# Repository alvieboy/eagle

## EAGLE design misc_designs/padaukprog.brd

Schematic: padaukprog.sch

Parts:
BOOT1, BOOT2: PIN-1X2
C1, C2, C3, C4, C7, C22, C24, C27, C47, C56: 100nF 6.3V; 0603
C5, C6, C41, C44: 22uF 16V; 0805
C8, C10, C11, C15, C29, C30, C33, C34, C35, C45, C50, C54, C64, C68, C69, C70, C71, C73, C74, C75, C76, C77, C80: 100nF; 0603
C9, C25, C26, C53, C57, C60, C63, C66: 100nF 50V; 0603
C12, C17, C18, C38, C48: 10uF; 0603
C13: 2.2uF 50V; 0805
C14: 2.2uF; 0603
C16: 2.2uF; 0805
C19, C20: 16pF 6.3V; 0603
C21, C36, C46, C61: 1uF; 0603
C23: 1nF; 0603
C28: 100nF/DNP; 0603
C31, C32, C81, C82: 20pF 6.3V; 0603
C37, C42, C51, C55, C62, C72, C78: 10uF; 0805
C39, C40, C67: 22uF; 0805
C43, C49, C52: 10uF 6.3V; 0603
C58, C59: 22uF 50V; 0805
C65, C79: 10nF; 0603
D1: 1N4148W; SOD-123
D2: 2SS100L-W; SOD-123
D3, D4: RB521S-30; SOD523
H1, H2, H3, H4, H5, H6, H7: MOUNT-PAD-ROUND3.2; 3,2-PAD
IC1: LAN8720A; QFN24_4MM_X_4MM
IC2: LM358D; SO08
IC3: IC_DIL16-SOIC-16; SOIC-16
IC4: TPS62063; WSON8-2.1X2.1
IC5: DIL16; DIL16@1
IC6, IC7: 4051D; SO16
IC8: PFS154-S16; SOIC16-N
IC9: MIC550X; SOT23-5L
J1, J4: JST-PH 2mm; JST-2-PTH@1
J2, J5: JUMPER_SOLDER_1X2
J3: JACK-PLUG; SPC4078-NOSLOT
J6: AVR_SPI_PRG_6NS; 2X3-NS
JP1, JP2, JP3, JP5, JP6, JP7, JP8, JP9: PIN-1X2
JP4: PIN-1X3
JP10: VBat +; PIN-1X2
JP11: Pedal; PIN-1X2
JP12, JP13: PIN-1X8
L1, L2, L3, L8, L9: 10uH; 0805
L4, L5, L7, L11, L12, L14: 600R; 0805
L6: 150nH; 0805
L10, L13: DFE252012F; L2520
LED1, LED2, LED3, LED4, LED5, LED6: LG L29K-G2J1-24; LED-603
M1, M2, M3: XT1861B; SOT23
P1, P2: B3B-PH-K
Q1, Q2, Q3, Q5, Q7, Q10: BSS84; SOT23
Q4: 25MHz; HC49U-V
Q6, Q11: 8MHz; HC49U-V
Q8: BSS123; SOT23
Q9: FDN338; SUPER-SOT3
R1: 470K; 0603
R2, R5, R8, R9, R10, R38, R42, R45: 2K2; 0603
R3, R4, R6, R7, R11, R22, R25, R36, R43, R52, R74, R75, R76, R81, R82, R83: 10K; 0603
R12, R14, R47, R48, R78, R79: 20R; 0603
R13, R15, R16, R17, R18, R19, R20, R21, R54, R55: 330R; 0603
R23, R24, R73: 240K; 0603
R26, R27, R28, R32, R34: 20K; 0603
R29, R64: 6K2; 0603
R30: 12K1; 0603
R31, R33, R63: 100K; 0603
R35, R37: 2K2/DNP; 0603
R39, R41, R44, R46: 49R9; 0603
R40, R65, R66, R67, R69: 0R; 0603
R49, R68, R70: 0R/DNP; 0603
R50, R51, R56, R57, R58, R59, R60, R61, R62: 100R; 0603
R53, R71, R72, R77, R80: 1K5/DNP; 0603
S1, S2, S3: SWITCHES_-SMD-1101NE; TACTILE-SWITCH-1101NE
SJ1: SOLDERJUMPERNC; SJ_2S_SMALL
T1: Hanrun HR917550A; HR13550A
TP11, TP12, TP13: TPPAD1-13; P1-13
TP14, TP15, TP16, TP17, TP18: TPTP07SQ; TP07SQ
TP20, TP21, TP22, TP23, TP24, TP25, TP26, TP27, TP28, TP29: TPTP12SQ; TP12SQ
U1: STM32F107RCT6; QFP50P1200X1200X160-64N
U2: ESP-WROOM-32
U3: MIC550X; SOT23-5L
U4: ATTINY24A-SSU; SOIC127P600X175-14N
U$1, U$8, U$10, U$12, U$22, U$30: PIN-1X4
U$2: STM32F072CBT6; LQFP48
U$3: SR410361N; LCD_7SEG_4DIGIT
U$4: STM8S003F3P6; TSSOP20
U$5: P25QXH; SOIC8
U$6, U$11, U$21, U$23: PIN-1X8
U$7, U$20: PFS154-S16; SOIC16-N
U$9: TSSOP16
U$13: PMS150C-U06; SOT23-6
U$14: AP2000; SOT23-6
U$15: MT3608; SOT23-6
U$16, U$17, U$18, U$26, U$27: PIN-1X10
U$19: STM32F030F4P6; TSSOP20
U$25: PN532_NFCB; HW-147-NFC-NOHOLES
U$28: MIC550X; SOT23-5L
U$29: STM32F070F6; TSSOP20
USB1, USB2, USB3: CON-USB-F-MICRO-B; CONN_USB_MICRO-B
VDD: TPTP10R; TP10R
VPP: TPTP10R; TP10R
X1, X2: FH12-40S-0.5SH

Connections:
+3V3: BOOT1.2, BOOT2.2, C1.1, C2.1, C3.1, C4.1, C8.2, C10.2, C11.2, C15.2, C16.2, C17.2, C22.1, C24.1, C27.1, C30.2, C33.2, C38.2, C39.2, C47.1, C48.2, C49.1, C50.2, C52.1, C62.2, C64.2, C65.2, C68.2, C69.2, C76.2, C77.2, C79.2, C80.2, IC1.1 (VDD2A), IC1.9 (VDDIO), IC1.19 (VDD1A), IC4.4 (FB), J2.2, J5.2, JP1.2, JP9.1, L1.1, L5.1, L11.2, L12.1, L13.P$2 (2), LED1.A, LED2.A, LED3.A, LED4.A, LED5.A, LED6.A, M1.3 (VOUT), M3.3 (VOUT), Q1.2 (S), Q2.2 (S), Q3.2 (S), Q5.2 (S), Q7.2 (S), Q9.2 (S), R1.1, R4.2, R6.2, R7.2, R8.2, R10.2, R11.2, R22.2, R25.2, R35.2, R36.2, R37.2, R52.2, R53.2, R54.2, R55.2, R63.1, R75.2, R80.2, R83.2, U1.1 (VBAT), U1.19 (VDD_4), U1.32 (VDD_1), U1.48 (VDD_2), U1.64 (VDD_3), U3.5 (VOUT), U$1.1, U$2.1 (VBAT), U$2.24 (VDD), U$2.36 (VDDIO2), U$2.48 (VDD), U$4.9 (VDD), U$5.3 (NWP), U$5.8 (VCC), U$7.5 (VCC), U$8.1, U$10.4, U$19.16 (VDD), U$22.2, U$23.7, U$25.VCC, U$25.VCC1 (VCC), U$28.5 (VOUT), U$29.5 (VDDA), U$29.16 (VDD), U$30.1, X1.2, X1.3
+5V: C40.2, L7.1, USB2.P1 (VUSB)
+5V_FILT: C43.1, L7.2, Q10.2 (S), R64.2, U3.1 (VIN), U3.3 (EN)
+15V: C9.1, C13.1, C57.1, C58.2, C59.2, D2.C, IC2.8 (V+), R73.2
A_MISO: J6.1, U4.8 (PA5)
A_MOSI: J6.4, U4.7 (PA6)
A_RESET: J6.5, U4.4 (PB3)
A_SCK: J6.3, U4.9 (PA4)
BOOT0: BOOT1.1, R43.2, U$2.38 (PA15), U$2.44 (BOOT0)
CA0: Q1.1 (G), R7.1, U$7.7 (PA6)
CA1: Q2.1 (G), R11.1, U$7.6 (PA7)
CA2: Q3.1 (G), R22.1, U$7.4 (PB7)
CA3: Q5.1 (G), R25.1, U$7.3 (PB6)
CC_RST: U1.39 (PC8), X1.22
CC_RX: U1.53 (PC12), X1.17
CC_SS: U1.40 (PC9), X1.21
CC_TX: U1.54 (PD2), X1.18
ESP_EN: U1.49 (PA14), U2.3 (EN)
ESP_IO0: U1.29 (PB10), U2.25 (IO0)
ESP_MISO: R67.2, R68.2, U2.31 (IO19)
ESP_MOSI: R69.2, R70.2, U2.37 (IO23)
ESP_ON: Q9.1 (G), R63.2
ESP_RX: U1.51 (PC10), U2.34 (RXD0)
ESP_SCK: R66.2, U2.30 (IO18)
ESP_TX: U1.52 (PC11), U2.35 (TXD0)
ESP_VCC: Q9.3 (D), U2.2 (3V3)
F_MISO: U$4.17 (PC7/SPI_MISO/[TIM1_CH2]), U$5.2 (SO)
F_MOSI: U$4.16 (PC6/SPI_MOSI/[TIM1_CH1]), U$5.5 (SI)
F_NCS: U$4.10 (PA3/TIM2_CH3/[SPI_NSS]), U$5.1 (NCS)
F_NHOLD: U$4.1 (PD4/UART1_CK/TIM2_CH1/BEEP), U$5.7 (NHOLD)
F_SCK: U$4.15 (PC5/SPI_SCK/[TIM2_CH1]), U$5.6 (SCK)
GND: C1.2, C2.2, C3.2, C4.2, C5.1, C6.1, C7.2, C8.1, C10.1, C11.1, C12.1, C14.1, C15.1, C16.1, C17.1, C18.1, C19.1, C20.1, C21.1, C22.2, C23.1, C24.2, C25.2, C26.2, C27.2, C28.1, C29.1, C30.1, C31.1, C32.1, C33.1, C34.2, C35.2, C36.1, C37.1, C38.1, C39.1, C40.1, C41.1, C42.1, C43.2, C44.1, C45.1, C46.1, C47.2, C48.1, C49.2, C50.1, C51.1, C52.2, C53.2, C54.1, C55.1, C56.2, C57.2, C58.1, C59.1, C60.2, C61.1, C62.1, C64.1, C65.1, C66.2, C67.1, C68.1, C69.1, C70.2, C71.1, C72.1, C73.2, C74.1, C75.2, C76.1, C77.1, C78.1, C79.1, C80.1, C81.1, C82.1, D4.K, IC1.P (VSS), IC4.1 (PGND), IC4.3 (AGND), IC4.6 (MODE), IC4.EXP (PGND), IC5.12, IC6.7 (VEE), IC6.8 (GND), IC7.7 (VEE), IC7.8 (GND), IC8.12 (GND), IC9.2 (GND), J1.2, J3.1, J4.2, J6.6, JP2.1, JP3.1, JP4.1, JP5.2, JP7.1, JP8.2, JP10.1, JP11.1, M1.1 (GND), M2.1 (GND), M3.1 (GND), P1.1, P2.3, Q8.2 (S), R3.2, R23.1, R24.1, R27.1, R29.1, R30.1, R32.1, R34.1, R43.1, R72.1, R74.1, R76.1, R82.1, S1.P$1 (1), S2.P$2 (2), S3.P$2 (2), TP11.TP, TP12.TP, TP13.TP, U1.12 (VSSA), U1.18 (VSS_4), U1.31 (VSS_1), U1.47 (VSS_2), U1.63 (VSS_3), U2.1 (GND), U2.15 (GND), U2.38 (GND), U2.GND, U3.2 (GND), U4.14 (GND), U$1.4, U$2.8 (VSSA), U$2.23 (VSS), U$2.35 (VSS), U$2.47 (VSS), U$4.7 (VSS), U$5.4 (GND), U$7.12 (GND), U$8.4, U$10.1, U$12.3, U$12.4, U$13.2 (GND), U$14.2 (GND), U$15.2 (GND), U$18.1, U$19.15 (VSS), U$20.12 (GND), U$22.1, U$23.8, U$25.GND, U$25.GND1 (GND), U$26.1, U$27.1, U$28.2 (GND), U$29.15 (VSS), U$30.4, USB1.P5 (GND), USB2.P5 (GND), USB3.P5 (GND), X1.4, X1.5, X1.11, X1.29, X1.31, X1.33, X1.35, X1.37, X1.40, X2.4, X2.5, X2.11, X2.29, X2.31, X2.33, X2.35, X2.37, X2.40
LCLK: U$7.11 (PA0), U$10.2
LDAT: U$7.13 (PB0), U$10.3
LED0: R2.2, U$2.2 (PC13)
LED1: R5.2, U$2.3 (PC14/OSC32_IN)
LED2: R9.2, U$2.4 (PC15/OSC32_OUT)
MCO: R40.1, U1.41 (PA8)
MCU_MISO: IC5.7, R59.1, R60.1, U$13.3 (PA6), U$20.7 (PA6)
MCU_MOSI: IC5.10, R61.1, R62.1, U$13.1 (PA4), U$20.10 (PA4)
MCU_PA0: IC5.11, R56.1, TP28.TP, U$20.11 (PA0)
MCU_PA7: IC5.6, R57.1, TP29.TP, U$20.6 (PA7)
MCU_SCK: IC5.9, R58.1, U$13.6 (PA3), U$20.9 (PA3)
MISO: R59.2, R62.2, U$2.40 (PB4)
MOSI: R60.2, R61.2, U$2.41 (PB5)
unnamed: LED2.C, R5.1
unnamed: C44.2, L10.P$1 (1), Q10.3 (D), U$15.4 (EN), U$15.5 (IN)
unnamed: LED3.C, R9.1
unnamed: L2.2, M1.2 (SW)
unnamed: C5.2, J2.1, JP3.2, L2.1
unnamed: TP17.TP, U$4.5 (PA1/OSCIN)
unnamed: C14.2, U$4.8 (VCAP)
unnamed: C29.2, R36.1, U$4.4 (NRST), U$8.2
unnamed: TP18.TP, U$4.6 (PA2/OSCOUT)
unnamed: C45.2, C46.2, L11.1, U$19.5 (VDDA)
unnamed: C36.2, JP6.1, L6.2
unnamed: TP14.TP, U$4.20 (PD3/AIN4/TIM2_CH2/ADC_ETR)
unnamed: C41.2, J4.1, J5.1, L8.1
unnamed: C37.2, JP6.2
unnamed: L6.1, Q7.3 (D), Q8.3 (D)
unnamed: L8.2, M3.2 (SW)
unnamed: L14.1, USB3.P1 (VUSB)
unnamed: Q7.1 (G), R49.1, R50.1
unnamed: Q8.1 (G), R51.1
unnamed: R12.1, USB1.P2 (D-)
unnamed: LED1.C, R2.1
unnamed: R14.1, USB1.P3 (D+)
unnamed: JP9.2, R76.2, U$19.1 (BOOT0)
unnamed: U$12.1, X2.1
unnamed: R65.2, U2.29 (IO5)
unnamed: LED4.C, R38.1
unnamed: LED5.C, R42.1
unnamed: LED6.C, R45.1
unnamed: R78.1, USB3.P2 (D-)
unnamed: IC5.16, TP23.TP
unnamed: IC5.15, TP22.TP
unnamed: IC5.14, TP21.TP
unnamed: R79.1, USB3.P3 (D+)
unnamed: IC6.3 (X), IC7.3 (X)
unnamed: IC5.13, TP20.TP
unnamed: R47.1, USB2.P2 (D-)
unnamed: R48.1, USB2.P3 (D+)
unnamed: IC6.4 (X7), JP12.1
unnamed: L4.1, USB1.P1 (VUSB)
unnamed: IC1.24 (RBIAS), R30.2
unnamed: C6.2, J1.1, L3.1
unnamed: R73.1, R74.2, U$15.3 (FB)
unnamed: C63.2, D3.K, D4.A
unnamed: C35.1, T1.5
unnamed: C34.1, T1.4
unnamed: R54.1, T1.12 (A)
unnamed: L3.2, M2.2 (SW)
unnamed: C18.2, JP5.1, M2.3 (VOUT)
unnamed: IC7.13 (X0), JP13.8
unnamed: IC2.6 (-IN), R28.2, R29.2
unnamed: IC2.2 (-IN), R26.2, R27.2
unnamed: IC6.13 (X0), JP12.8
unnamed: R55.1, T1.9 (A)
unnamed: IC5.1, TP24.TP
unnamed: IC5.2, TP25.TP
unnamed: C28.2, L5.2, R39.2, R41.2, R44.2, R46.2
unnamed: IC5.3, TP26.TP
unnamed: C21.2, C23.2, IC1.6 (VDDCR)
unnamed: IC5.4, TP27.TP
unnamed: IC6.14 (X1), JP12.7
unnamed: IC6.12 (X3), JP12.5
unnamed: IC6.1 (X4), JP12.4
unnamed: IC6.5 (X5), JP12.3
unnamed: IC6.2 (X6), JP12.2
unnamed: Q2.3 (D), U$3.9 (CA1)
unnamed: J6.2, SJ1.2
unnamed: IC7.14 (X1), JP13.7
unnamed: IC7.15 (X2), JP13.6
unnamed: IC7.12 (X3), JP13.5
unnamed: IC6.15 (X2), JP12.6
unnamed: IC7.1 (X4), JP13.4
unnamed: IC7.5 (X5), JP13.3
unnamed: IC7.2 (X6), JP13.2
unnamed: IC7.4 (X7), JP13.1
unnamed: Q3.3 (D), U$3.8 (CA2)
unnamed: Q1.3 (D), U$3.12 (CA0)
unnamed: Q5.3 (D), U$3.6 (CA3)
unnamed: U$12.2, U$17.1, X2.2, X2.3
unnamed: IC3.8, U$6.1, U$9.1
unnamed: IC3.7, U$6.2, U$9.2
unnamed: IC3.6, U$6.3, U$9.3
unnamed: IC3.5, U$6.4, U$9.4
unnamed: IC3.4, U$6.5, U$9.5
unnamed: IC3.3, U$6.6, U$9.6
unnamed: IC3.2, U$6.7, U$9.7
unnamed: IC3.1, U$6.8, U$9.8
unnamed: IC3.16, U$9.9, U$11.8
unnamed: IC3.15, U$9.10, U$11.7
unnamed: IC3.13, U$9.12, U$11.5
unnamed: IC3.14, U$9.11, U$11.6
unnamed: IC3.12, U$9.13, U$11.4
unnamed: IC3.11, U$9.14, U$11.3
unnamed: IC3.10, U$9.15, U$11.2
unnamed: IC3.9, U$9.16, U$11.1
NBOOT0: BOOT2.1, R82.2, U$29.1 (BOOT0)
NIRQ: U$25.IRQ, U$29.7 (PA1)
NLED0: R38.2, U1.46 (PA13)
NLED1: R42.2, U1.35 (PB14)
NLED2: R45.2, U1.36 (PB15)
NNRST: R83.1, S3.P$1 (1), U$29.4 (NRST)
NOSC_IN: C81.2, Q11.2, U$29.2 (PF0/OSC_IN)
NOSC_OUT: C82.2, Q11.1, U$29.3 (PF1/OSC_OUT)
NRST: R52.1, S2.P$1 (1), U$2.7 (NRST)
NRSTO: U$25.RSTO, U$29.6 (PA0)
NSWCLK: U$29.20 (PA14), U$30.3
NSWDIO: U$29.19 (PA13), U$30.2
NUSBDM: R78.2, U$29.17 (PA9/PA11)
NUSBDP: R79.2, R80.1, U$29.18 (PA10/PA12)
N_MISO: U$25.MISO, U$29.12 (PA6)
N_MOSI: U$25.MOSI, U$29.13 (PA7)
N_RX: U$25.SDA/TX, U$29.9 (PA3)
N_SCK: U$25.SCK, U$29.11 (PA5)
N_SS: U$25.SS, U$29.10 (PA4)
N_TX: U$25.SCL/RX, U$29.8 (PA2)
OSC_IN: C31.2, Q6.2, U$2.5 (PF0/OSC_IN)
OSC_OUT: C32.2, Q6.1, U$2.6 (PF1/OSC_OUT)
PA0: U$19.6 (PA0), U$23.3
PA1: U$19.7 (PA1), U$23.2
PA2: U$19.8 (PA2), U$23.1
PA3: U$19.9 (PA3), U$21.8
PA3/ADC3: U1.17 (PA3), X1.30
PA4: U$19.10 (PA4), U$21.7
PA4/DAC1: U1.20 (PA4), X1.32
PA5: U$19.11 (PA5), U$21.6
PA5/DAC2: U1.21 (PA5), X1.34
PA6: U$19.12 (PA6), U$21.5
PA7: U$19.13 (PA7), U$21.4
PA9: P2.2, U$19.17 (PA9)
PA10: P2.1, U$19.18 (PA10)
PA13: U$19.19 (PA13/SWDIO), U$21.2
PA14: U$19.20 (PA14/SWCLK), U$21.1
PA15/NSS: R65.1, U1.50 (PA15)
PB1: U$19.14 (PB1), U$21.3
PB6/UART1_TX: U1.58 (PB6), X1.12
PB7/UART1_RX: U1.59 (PB7), X1.13
PEDAL: JP11.2, R81.1, U4.5 (PB2)
PF0: U$19.2 (PF0/OSC_IN), U$23.6
PF1: U$19.3 (PF1/OSC_OUT), U$23.5
PHY_LED0: IC1.3 (LED1/REGOFF), T1.10 (K)
PHY_LED1: IC1.2 (LED2/NINTSEL), T1.11 (K)
PWM1: R50.2, R51.2, U$4.13 (PC3/TIM1_CH3/[TIM1_CH1N])
PWM2: R49.2, U$4.14 (PC4/TIM1_CH4/CLK_CCO/AIN2/[TIM1_CH2N])
PWRON: Q10.1 (G), R64.1, U$2.27 (PB14)
REG33IN: C51.2, D1.1 (C), IC4.5 (EN), IC4.7 (AVIN), IC4.8 (PVIN), J3.3, X1.1
RMII_CRS_DV: IC1.11 (CRS_DV/MODE2), U1.23 (PA7)
RMII_MDC: IC1.13 (MDC), R8.1, U1.9 (PC1)
RMII_MDIO: IC1.12 (MDIO), R10.1, U1.16 (PA2)
RMII_NRST: IC1.15 (NRST), R4.1, U1.22 (PA6)
RMII_REF_CLK: IC1.14 (NINT/REFCLK0), U1.15 (PA1)
RMII_RXD0: IC1.8 (RXD0/MODE0), U1.24 (PC4)
RMII_RXD1: IC1.7 (RXD1/MODE1), U1.25 (PC5)
RMII_TXD0: IC1.17 (TXD0), U1.33 (PB12)
RMII_TXD1: IC1.18 (TXD1), U1.34 (PB13)
RMII_TX_EN: IC1.16 (TXEN), U1.30 (PB11)
RX: JP4.2, U$4.3 (PD6/UART1_RX/AIN6)
RXM1: IC1.20 (TXN), R41.1, T1.2
RXP1: IC1.21 (TXP), R39.1, T1.1
S0: U$16.1, X2.6
S1: U$18.2, X2.7
S2: U$17.2, X2.8
S3: U$16.2, X2.9
S4: U$18.3, X2.10
S5: U$17.3, X2.12
S6: U$16.3, X2.13
S7: U$18.4, X2.14
S8: U$17.4, X2.15
S9: U$16.4, X2.16
S10: U$18.5, X2.17
S11: U$17.5, X2.18
S12: U$16.5, X2.19
S13: U$18.6, X2.20
S14: U$17.6, X2.21
S15: U$16.6, X2.22
S16: U$18.7, X2.23
S17: U$17.7, X2.24
S18: U$16.7, X2.25
S19: U$18.8, X2.26
S20: U$17.8, X2.27
S21: U$16.8, X2.28
S22: U$18.9, X2.30
S23: U$17.9, X2.32
S24: U$16.9, X2.34
S25: U$18.10, X2.36
S26: U$17.10, X2.38
S27: U$16.10, X2.39
SA: R13.2, U$3.11 (A)
SB: R15.2, U$3.7 (B)
SC: R16.2, U$3.4 (C)
SCK: R58.2, U$2.39 (PB3)
SCL: TP15.TP, U$4.12 (PB4/I2C_SCL/ADC_ETR)
SD: R17.2, U$3.2 (D)
SDA: TP16.TP, U$4.11 (PB5/I2C_SDA/[TIM1_BKIN])
SDP: R21.2, U$3.3 (DP)
SE: R18.2, U$3.1 (E)
SEG_A: R13.1, U$7.9 (PA3)
SEG_B: R15.1, U$7.14 (PB1)
SEG_C: R16.1, U$7.2 (PB5)
SEG_D: R17.1, U$7.15 (PB2)
SEG_DP: R21.1, U$7.16 (PB3)
SEG_E: R18.1, U$7.10 (PA4)
SEG_F: R19.1, U$7.8 (PA5)
SEG_G: R20.1, U$7.1 (PB4)
SEL_A0: IC7.11 (A), U4.10 (PA3)
SEL_A1: IC6.11 (A), U4.13 (PA0)
SEL_B0: IC7.10 (B), U4.6 (PA7)
SEL_B1: IC6.10 (B), U4.12 (PA1)
SEL_C0: IC7.9 (C), U4.2 (PB0)
SEL_C1: IC6.9 (C), U4.11 (PA2)
SEL_INH: IC6.6 (INH), IC7.6 (INH), U4.3 (PB1)
SF: R19.2, U$3.10 (F)
SG: R20.2, U$3.5 (G)
SHIELD: T1.8, T1.Z1 (SHIELD), T1.Z2 (SHIELD)
STM_PA0: R56.2, U$2.42 (PB6)
STM_PA7: R57.2, U$2.43 (PB7)
SW: JP2.2, R6.1, U$4.19 (PD2/AIN3/[TIM2_CH3])
SWCLK: U$1.3, U$2.37 (PA14)
SWDIO: U$1.2, U$2.34 (PA13)
SWIM: U$4.18 (PD1/SWIM), U$8.3
S_FB: R71.1, R72.2, U$14.3 (FB)
S_SW: L9.2, U$14.1 (SW)
S_VIN: C42.2, JP7.2, L9.1, U$14.4 (SHDN), U$14.6 (VIN)
S_VOUT: C54.2, C55.2, JP8.1, R71.2, U$14.5 (VOUT)
TX: JP4.3, U$4.2 (PD5/UART1_TX/AIN5)
TXM1: IC1.22 (RXN), R46.1, T1.6
TXP1: IC1.23 (RXP), R44.1, T1.3
UART1RX: U1.43 (PA10), X1.19
UART1TX: U1.42 (PA9), X1.20
UART_RX: P1.2, U$2.31 (PA10)
UART_TX: P1.3, U$2.30 (PA9)
USBDM: R47.2, U$2.32 (PA11)
USBDP: R48.2, R53.1, U$2.33 (PA12)
USBPWR: D1.2 (A), L4.2
USBPWR1: C78.2, L14.2, U$28.1 (VIN), U$28.3 (EN)
VCC3: C71.2, C74.2, IC8.5 (VCC), IC9.5 (VOUT), R77.2, U$26.9, U$26.10
VCCI: C67.2, IC9.1 (VIN), IC9.3 (EN), R77.1, U$27.9, U$27.10
VDDA: C56.1, L12.2, U$2.9 (VDDA)
VDD_OUT: C25.1, C53.1, IC2.1 (OUT), IC5.5, R26.1, R33.2, U$13.5 (VCC), U$20.5 (VCC), VDD.TP
VDD_PWM: IC2.3 (+IN), R23.2, U$2.15 (PA5)
VDD_SENS: R33.1, R34.2, U$2.19 (PB1)
VEE: C9.2, C13.2, C66.1, D3.A, IC2.4 (V-)
VNEG_PWM: C63.1, U$2.13 (PA3)
VPP_OUT: C26.1, C60.1, IC2.7 (OUT), IC5.8, R28.1, R31.2, U$13.4 (PA5), U$20.8 (PA5), VPP.TP
VPP_PWM: IC2.5 (+IN), R24.2, U$2.14 (PA4)
VPP_SENS: R31.1, R32.2, U$2.18 (PB0)
VSW: D2.A, L10.P$2 (2), U$15.1 (SW)
V_BATT: C70.1, C72.2, C73.1, C75.1, IC6.16 (VCC), IC7.16 (VCC), JP10.2, R81.2, SJ1.1, U4.1 (VCC)
X0: IC8.1 (PB4), U$26.2
X1: IC8.2 (PB5), U$26.3
X2: IC8.3 (PB6), U$26.4
X3: IC8.4 (PB7), U$26.5
X4: IC8.6 (PA7), U$26.6
X5: IC8.7 (PA6), U$26.7
X6: IC8.8 (PA5), U$26.8
X7: IC8.16 (PB3), U$27.2
X8: IC8.15 (PB2), U$27.3
X9: IC8.14 (PB1), U$27.4
X10: IC8.13 (PB0), U$27.5
X11: IC8.11 (PA0), U$27.6
X12: IC8.10 (PA4), U$27.7
X13: IC8.9 (PA3), U$27.8
XBOOT0: JP1.1, R3.1, U1.60 (BOOT0)
XI: IC1.5 (XTAL1/CLKIN), R40.2
XNRST: C61.2, R75.1, U$19.4 (NRST), U$23.4
XOSC_IN: C19.2, Q4.2, U1.5 (PD0_OSC_IN)
XOSC_OUT: C20.2, Q4.1, U1.6 (PD1_OSC_OUT)
XPA0: U1.14 (PA0-WKUP), X1.28
XPB0/ADC8: U1.26 (PB0), X1.36
XPB1: U1.27 (PB1), X1.38
XPB2: U1.28 (PB2), X1.39
XPC0: U1.8 (PC0), X1.25
XPC2: U1.10 (PC2), X1.26
XPC3: U1.11 (PC3), X1.27
XPC6: U1.37 (PC6), X1.24
XPC7: U1.38 (PC7), X1.23
XPC13: U1.2 (PC13-TAMPER-RTC), X1.14
XPC14: U1.3 (PC14-OSC32_IN), X1.15
XPC15: U1.4 (PC15-OSC32_OUT), X1.16
XSCL: R35.1, U1.61 (PB8), U$22.3, X1.6
XSDA: R37.1, U1.62 (PB9), U$22.4, X1.7
XSPI_MISO: R67.1, R70.1, U1.56 (PB4), X1.9
XSPI_MOSI: R68.1, R69.1, U1.57 (PB5), X1.10
XSPI_SCK: R66.1, U1.55 (PB3), X1.8
XSW: IC4.2 (SW), L13.P$1 (1)
XUSBDM: R12.2, U1.44 (PA11)
XUSBDP: R14.2, U1.45 (PA12)
XVDDA: C7.1, C12.2, L1.2, U1.13 (VDDA)
XXNRST: R1.2, S1.P$2 (2), U1.7 (NRST)

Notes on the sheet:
STM32F070F6
-2.4V
REVER load
Ethernet PHY, Magnetics
USB connector
OLED
15mA
ALD192/1-1
PADAUK Programmer
AUDIO player
ALD192/2-1
ALD192/3-1
Battery-powered STM32030
ALD192/4-1
ETH Bridge
ALD192/9-1
ALD192/5-1
LCD Display
STEP UP Adjustable
PADAUK breakout
NFC USBizer
Attiny switch
ALD192/6-1
ALD192/7-1
ALD192/8-1
ALD192/10-1
SOIC16/TSSOP16 Addaptor

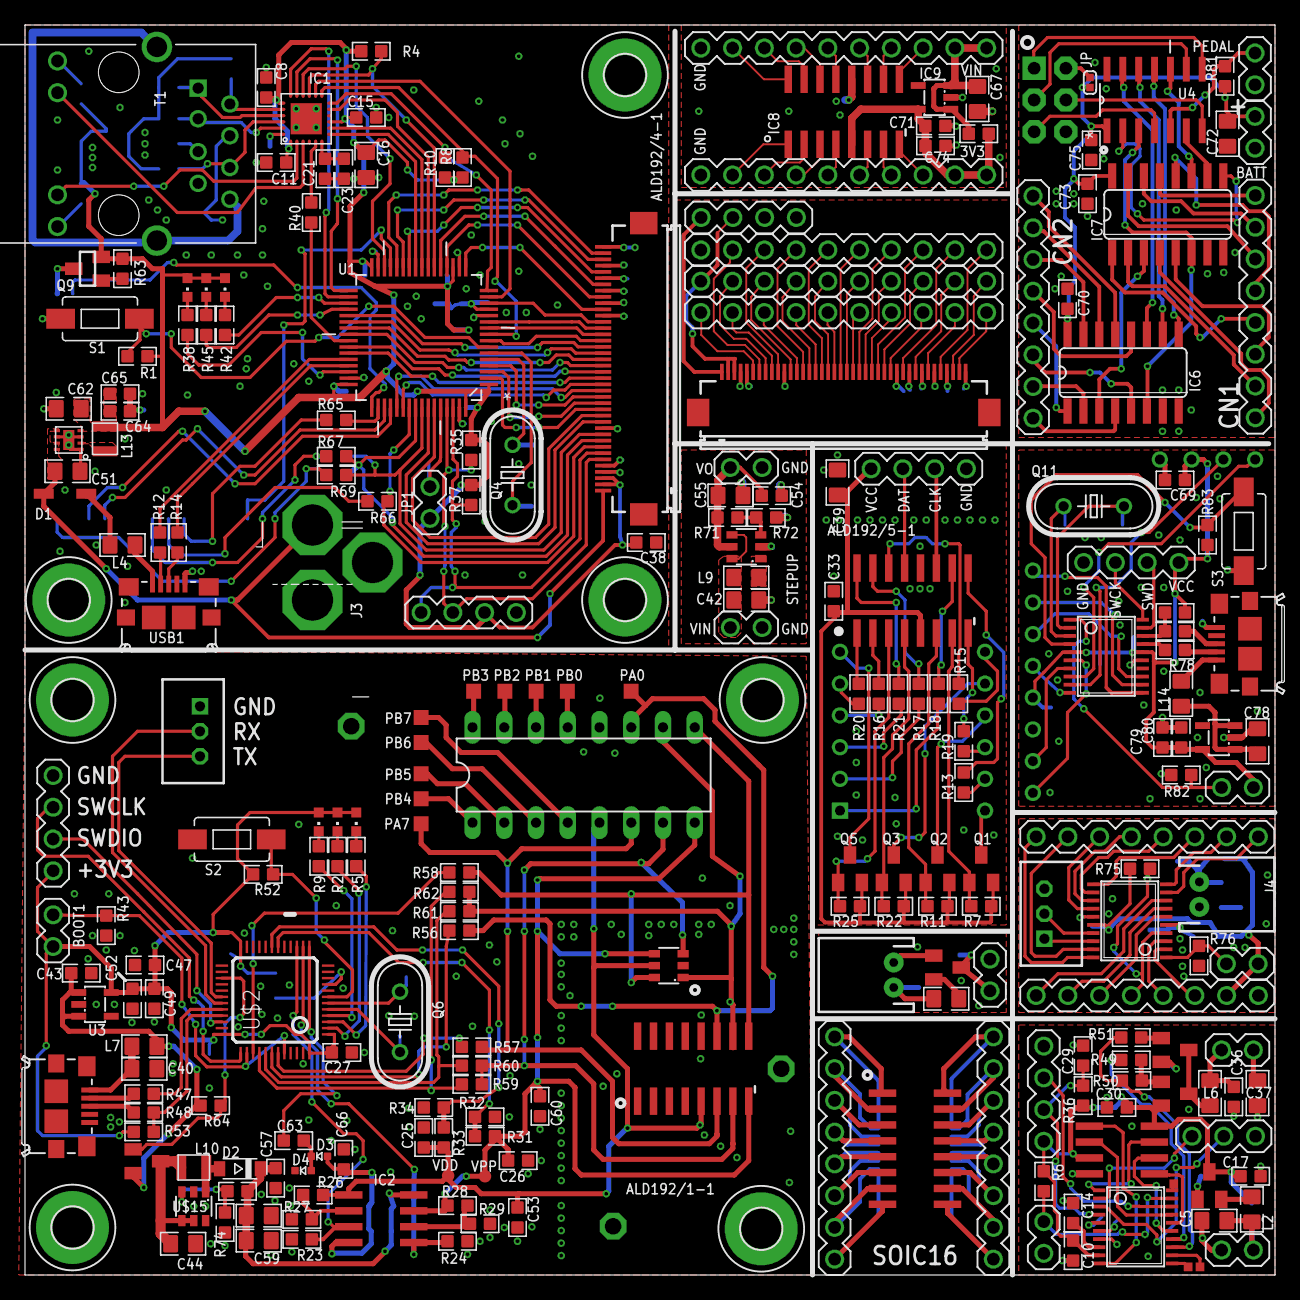
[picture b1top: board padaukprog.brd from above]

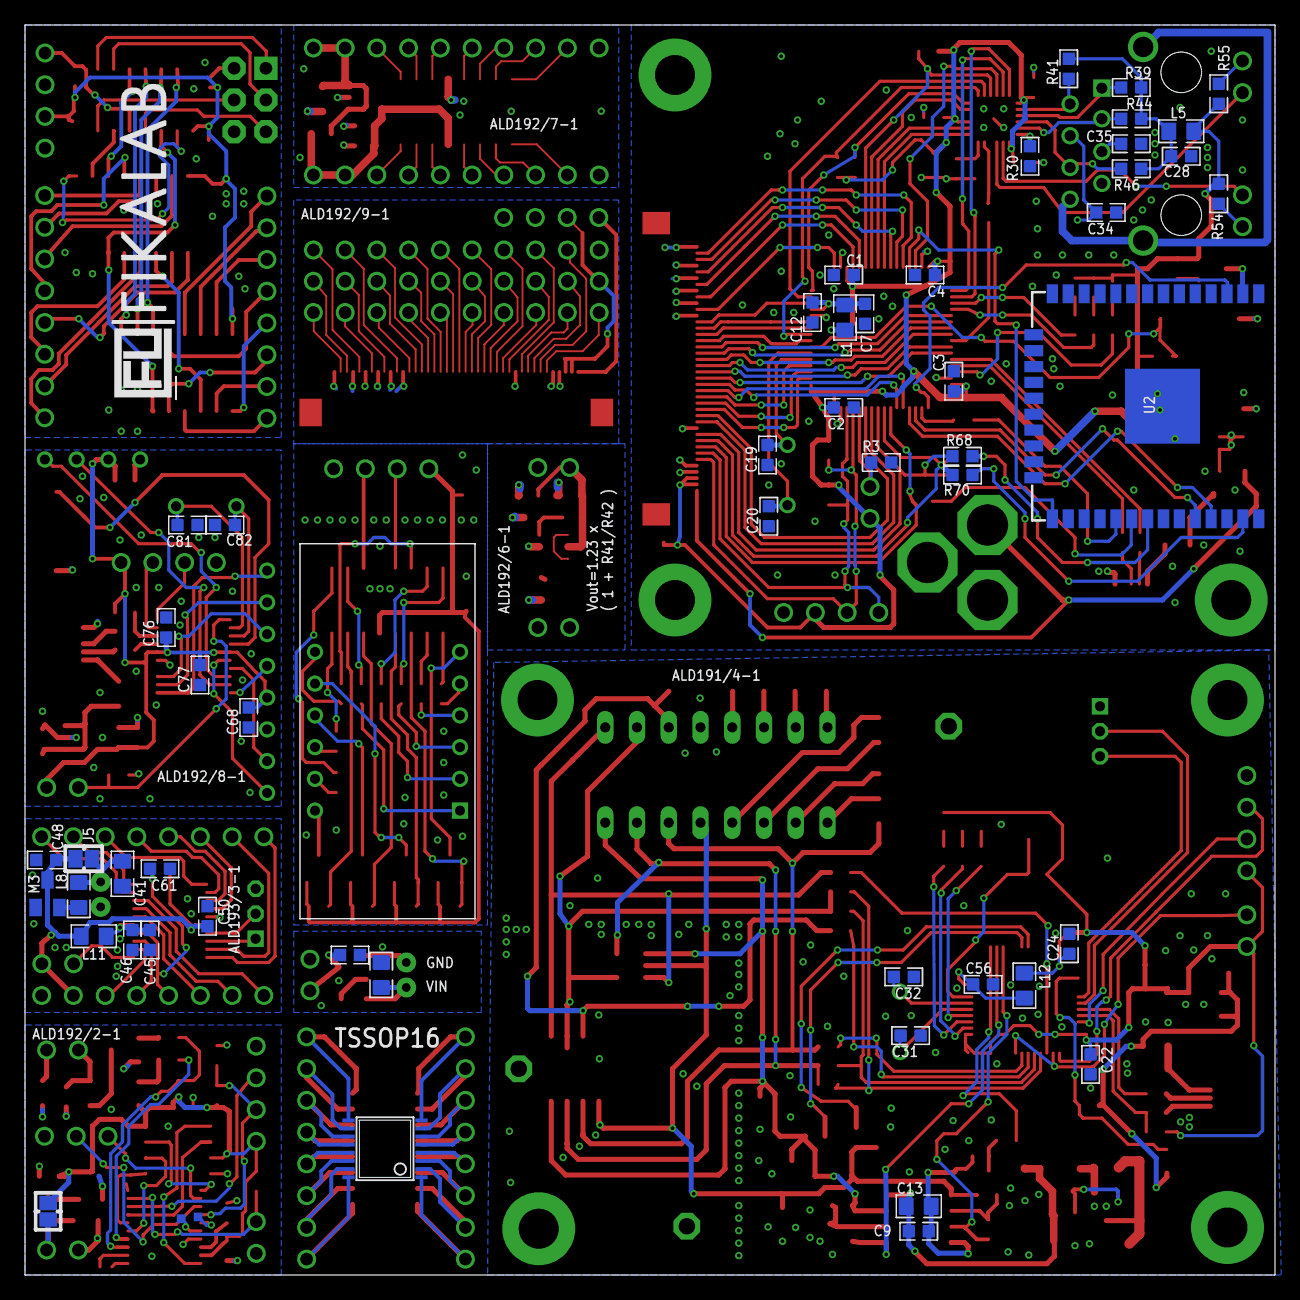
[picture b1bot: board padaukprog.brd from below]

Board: 3 copper layers, 100.0 x 100.0 mm, 306 parts (56 on the bottom side), 332 nets.

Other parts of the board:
U$24: FIKALAB-25X5

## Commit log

2019-03-03 Add libraries
2019-03-03 fix routing
2019-06-20 Sync models
2019-12-08 Add padauk prog + friends
2019-12-11 Add minimal STM32F030
2019-12-11 Cleanup
2019-12-15 Update lib
2019-12-15 Rotate design
2019-12-18 Wip for Zigbee
2019-12-18 Final routed
2019-12-20 Production
2019-12-20 Add gerbers

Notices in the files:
parts and their libraries:
con-jst-ph: Copyright (C) 2016, Bob Starr
SparkFun-Connectors: Licensing: Creative Commons ShareAlike 4.0 International - https://creativecommons.org/licenses/by-sa/4.0
SparkFun-Aesthetics: Licensing: CC v3.0 Share-Alike You are welcome to use this library for commercial purposes.
